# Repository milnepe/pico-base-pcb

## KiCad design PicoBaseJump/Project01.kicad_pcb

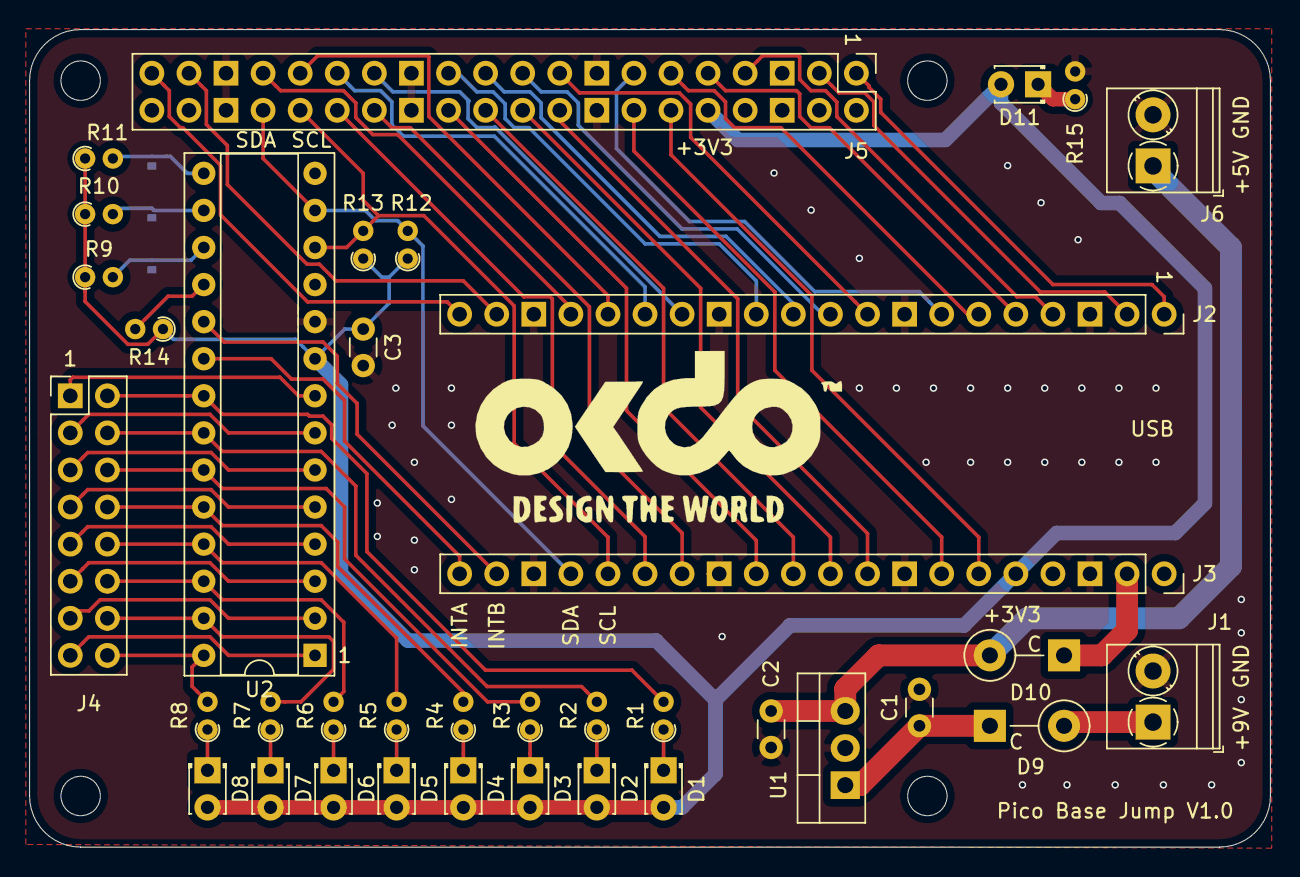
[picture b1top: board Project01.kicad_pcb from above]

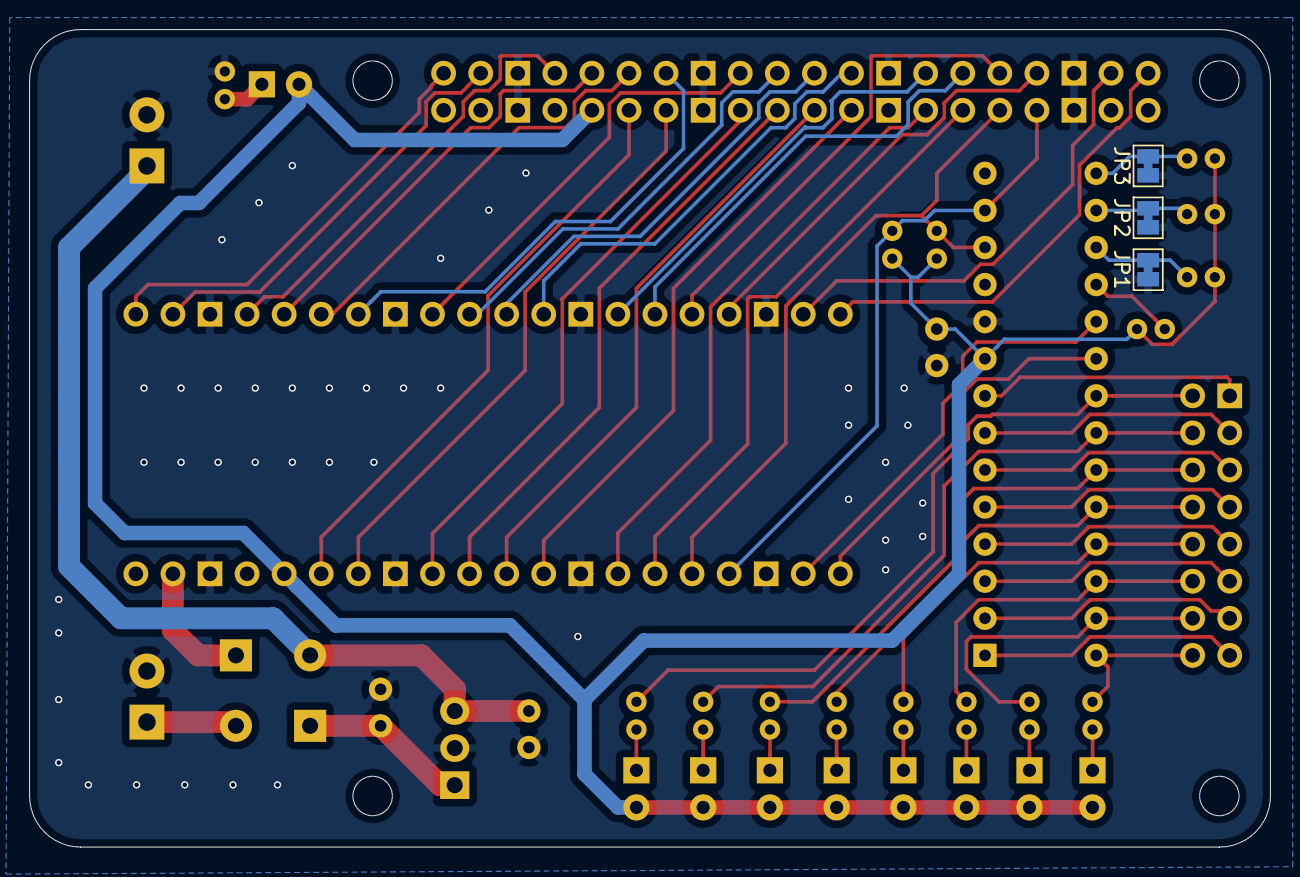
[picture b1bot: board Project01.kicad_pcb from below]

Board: 2 copper layers, 85.0 x 56.0 mm, 44 parts (3 on the bottom side), 63 nets.

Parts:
C1: 330nF; C_Disc_D3.0mm_W1.6mm_P2.50mm
C2, C3: 100nF; C_Disc_D3.0mm_W1.6mm_P2.50mm
D1, D2, D3, D4, D5, D6, D7, D8: RLED; LED_D1.8mm_W3.3mm_H2.4mm
D9: 1N4001; D_DO-41_SOD81_P5.08mm_Vertical_KathodeUp
D10: 1N5817; D_DO-41_SOD81_P5.08mm_Vertical_KathodeUp
D11: PWR_LED; LED_D1.8mm_W3.3mm_H2.4mm
H1, H2, H3, H4: MountingHole; MountingHole_2.7mm_M2.5
J1, J6: Terminal; TerminalBlock_Phoenix_PT-1,5-2-3.5-H_1x02_P3.50mm_Horizontal
J2: Conn_01x20_Female; PinSocket_1x20_P2.54mm_Pico_1_20
J3: Conn_01x20_Female; PinSocket_1x20_P2.54mm_Pico_21_40
J4: Conn_02x08_Odd_Even; PinHeader_2x08_P2.54mm_Vertical
J5: Conn_02x20_Counter_Clockwise; PinHeader_2x20_P2.54mm_Vertical_Pico
JP1, JP2, JP3: SolderJumper; SolderJumper-2_P1.3mm_Bridged_Pad1.0x1.5mm
R1, R2, R3, R4, R5, R6, R7, R8, R15: 1K7; R_Axial_DIN0204_L3.6mm_D1.6mm_P1.90mm_Vertical
R9, R10, R11, R14: 10K; R_Axial_DIN0204_L3.6mm_D1.6mm_P1.90mm_Vertical
R12, R13: 4K7; R_Axial_DIN0204_L3.6mm_D1.6mm_P1.90mm_Vertical
U1: L7805; TO-220-3_Vertical
U2: MCP23017_SP; DIP-28_W7.62mm_Socket

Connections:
+3V3: C3.1, D1.2, D2.2, D3.2, D4.2, D5.2, D6.2, D7.2, D8.2, D11.2, J3.36, J5.36, R9.1, R10.1, R11.1, R12.1, R13.1, R14.1, U2.9
+5V: C2.1, D10.2, J6.1, U1.3
A0: JP3.2, R11.2, U2.15
A1: JP2.2, R10.2, U2.16
A2: JP1.2, R9.2, U2.17
ADC_VREF: J3.35, J5.35
GND: C1.2, C2.2, C3.2, J1.2, J2.3, J2.8, J2.13, J2.18, J3.23, J3.28, J3.33, J3.38, J5.3, J5.8, J5.13, J5.18, J5.23, J5.28, J5.33, J5.38, J6.2, JP1.1, JP2.1, JP3.1, R15.2, U1.2, U2.10
GP0: J2.1, J5.1
GP1: J2.2, J5.2
GP2: J2.4, J5.4
GP3: J2.5, J5.5
GP4: J2.6, J5.6
GP5: J2.7, J5.7
GP6: J2.9, J5.9
GP7: J2.10, J5.10
GP8: J2.11, J5.11
GP9: J2.12, J5.12
GP10: J2.14, J5.14
GP11: J2.15, J5.15
GP12: J2.16, J5.16
GP13: J2.17, J5.17
GP14: J2.19, J5.19
GP15: J2.20, J5.20
GP20: J3.26, J5.26
GP21: J3.27, J5.27
GP22: J3.29, J5.29
GP26: J3.31, J5.31
GP27: J3.32, J5.32
GP28: J3.34, J5.34
GPA0: J4.2, R1.2, U2.21
GPA1: J4.4, R2.2, U2.22
GPA2: J4.6, R3.2, U2.23
GPA3: J4.8, R4.2, U2.24
GPA4: J4.10, R5.2, U2.25
GPA5: J4.12, R6.2, U2.26
GPA6: J4.14, R7.2, U2.27
GPA7: J4.16, R8.2, U2.28
GPB0: J4.15, U2.1
GPB1: J4.13, U2.2
GPB2: J4.11, U2.3
GPB3: J4.9, U2.4
GPB4: J4.7, U2.5
GPB5: J4.5, U2.6
GPB6: J4.3, U2.7
GPB7: J4.1, U2.8
I2C1_SCL: J3.25, J5.25, R13.2, U2.12
I2C1_SDA: J3.24, J5.24, R12.2, U2.13
INTA: J3.21, U2.20
INTB: J3.22, U2.19
unnamed: C1.1, D9.1, U1.1
unnamed: D1.1, R1.1
unnamed: D2.1, R2.1
unnamed: D3.1, R3.1
unnamed: D4.1, R4.1
unnamed: D5.1, R5.1
unnamed: D6.1, R6.1
unnamed: D7.1, R7.1
unnamed: D8.1, R8.1
unnamed: D11.1, R15.1
RESET: R14.2, U2.18
RUN: J3.30, J5.30
VCC: D9.2, J1.1
VSYS: D10.1, J3.39

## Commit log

2021-09-24 Add Kicad and C firmware
